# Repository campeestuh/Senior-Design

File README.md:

Circuit Wiring:

Rotary Encoder   --> FREENOVE ESP32 WROOM
> CLK (Output A) --> Pin 4 
> DT  (Output B) --> Pin 5 
> SW  (Switch)   --> Pin 16 
>  +  (VCC)      --> 5V 
> GND            --> GND

LCD 
VCC                 --> 5V
SDA (Serial Data)   --> Pin 21
SCL (Serial Clock)  --> Pin 22
GND                 --> GND

Button 
GND    --> GND
Signal --> Pin 19

Harness
STEP/PUL    --> Pin 15
DIRECTION   --> Pin 16
ENABLE      --> 5V

AUGER 
STEP/PUL    --> Pin 13
DIRECTION   --> Pin 14
ENABLE      --> 5V

AUGER 2 
STEP/PUL    --> Pin 33
DIRECTION   --> Pin 32
ENABLE      --> 5V

TREADMILL
STEP/PUL    --> Pin 27
DIRECTION   --> Pin 25
ENABLE      --> 5V

Arduino IDE
Board: ESP32 Wrover Module
How to get ESP32 Board Support:
- Go to File > Preferences
- In "Additional Board Manager URLs" add this URL:
https://dl.espressif.com/dl/package_esp32_index.json
- Click OK and save
- 
Install LiquidCrystal Library by Adafruit

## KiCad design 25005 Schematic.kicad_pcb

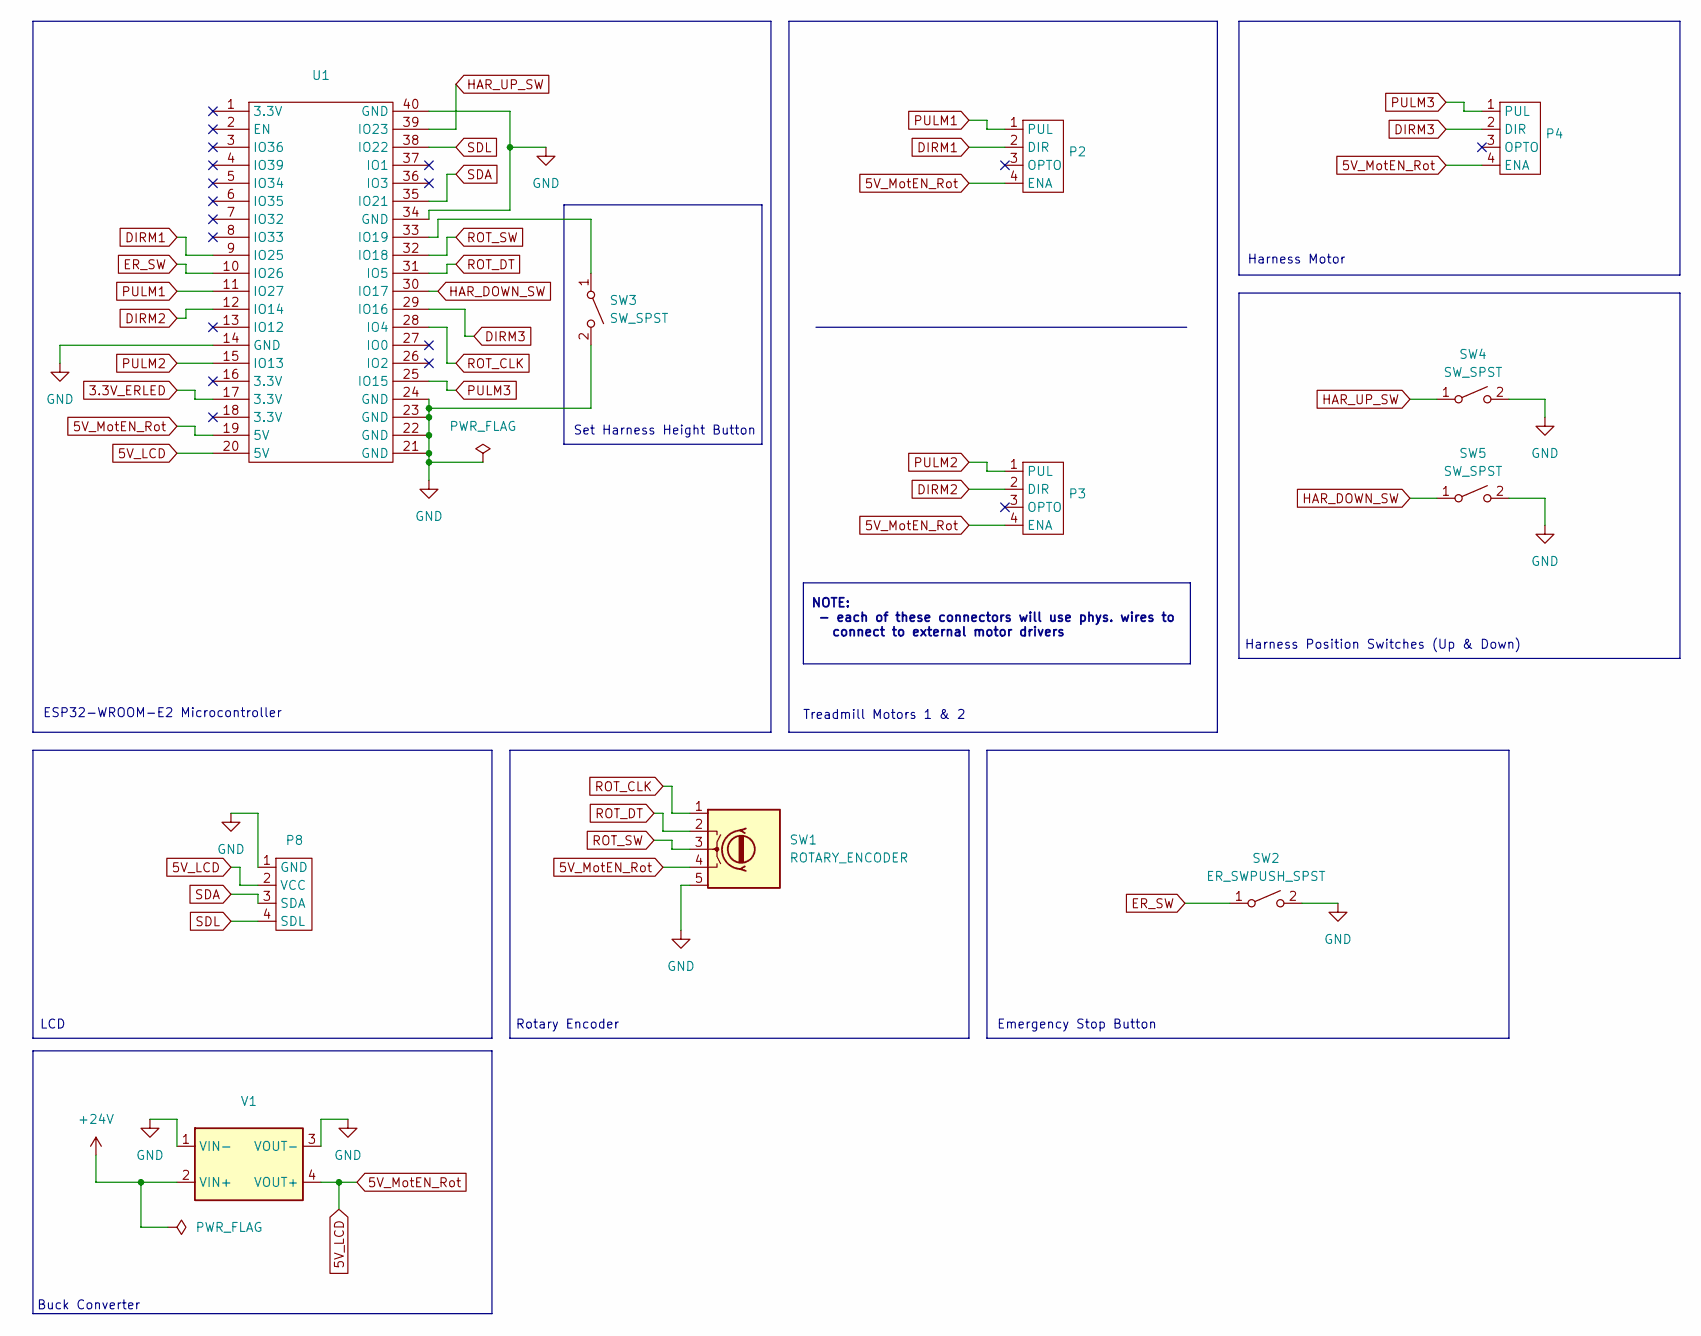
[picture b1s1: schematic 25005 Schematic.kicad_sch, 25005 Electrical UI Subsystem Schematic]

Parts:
P2, P3, P4: 3PIN_F_CONN_MOTORS
P8: 4PIN_F_CONN_LCD
SW1: ROTARY_ENCODER; 5PIN_F_CONN
SW2: ER_SWPUSH_SPST; ER_BUTTON
SW3, SW4, SW5: SW_SPST; SPST_SW
U1: ESP32_WROOM_32E
V1: BUCK_CONV

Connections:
3.3V_ERLED: U1.17 (3.3V)
5V_LCD: P2.4 (ENA), P3.4 (ENA), P4.4 (ENA), P8.2 (VCC), SW1.4 (5V), U1.19 (5V), U1.20 (5V), V1.4 (VOUT+)
+24V: V1.2 (VIN+)
DIRM1: P2.2 (DIR), U1.9 (IO25)
DIRM2: P3.2 (DIR), U1.12 (IO14)
DIRM3: P4.2 (DIR), U1.29 (IO16)
ER_SW: SW2.1, U1.10 (IO26)
GND: P8.1 (GND), SW1.5 (GND), SW2.2, SW3.2, SW4.2, SW5.2, U1.14 (GND), U1.21 (GND), U1.22 (GND), U1.23 (GND), U1.24 (GND), U1.34 (GND), U1.40 (GND), V1.1 (VIN-), V1.3 (VOUT-)
HAR_DOWN_SW: SW5.1, U1.30 (IO17)
HAR_UP_SW: SW4.1, U1.39 (IO23)
unnamed: SW3.1, U1.33 (IO19)
PULM1: P2.1 (PUL), U1.11 (IO27)
PULM2: P3.1 (PUL), U1.15 (IO13)
PULM3: P4.1 (PUL), U1.25 (IO15)
ROT_CLK: SW1.1 (CLK), U1.28 (IO4)
ROT_DT: SW1.2 (DT), U1.31 (IO5)
ROT_SW: SW1.3 (SW), U1.32 (IO18)
SDA: P8.3 (SDA), U1.35 (IO21)
SDL: P8.4 (SDL), U1.38 (IO22)

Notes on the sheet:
Harness Motor
ESP32-WROOM-E2 Microcontroller
Rotary Encoder
NOTE: - each of these connectors will use phys. wires to connect to external motor drivers
Set Harness Height Button
Harness Position Switches (Up & Down)
Emergency Stop Button
Treadmill Motors 1 & 2
Buck Converter
LCD

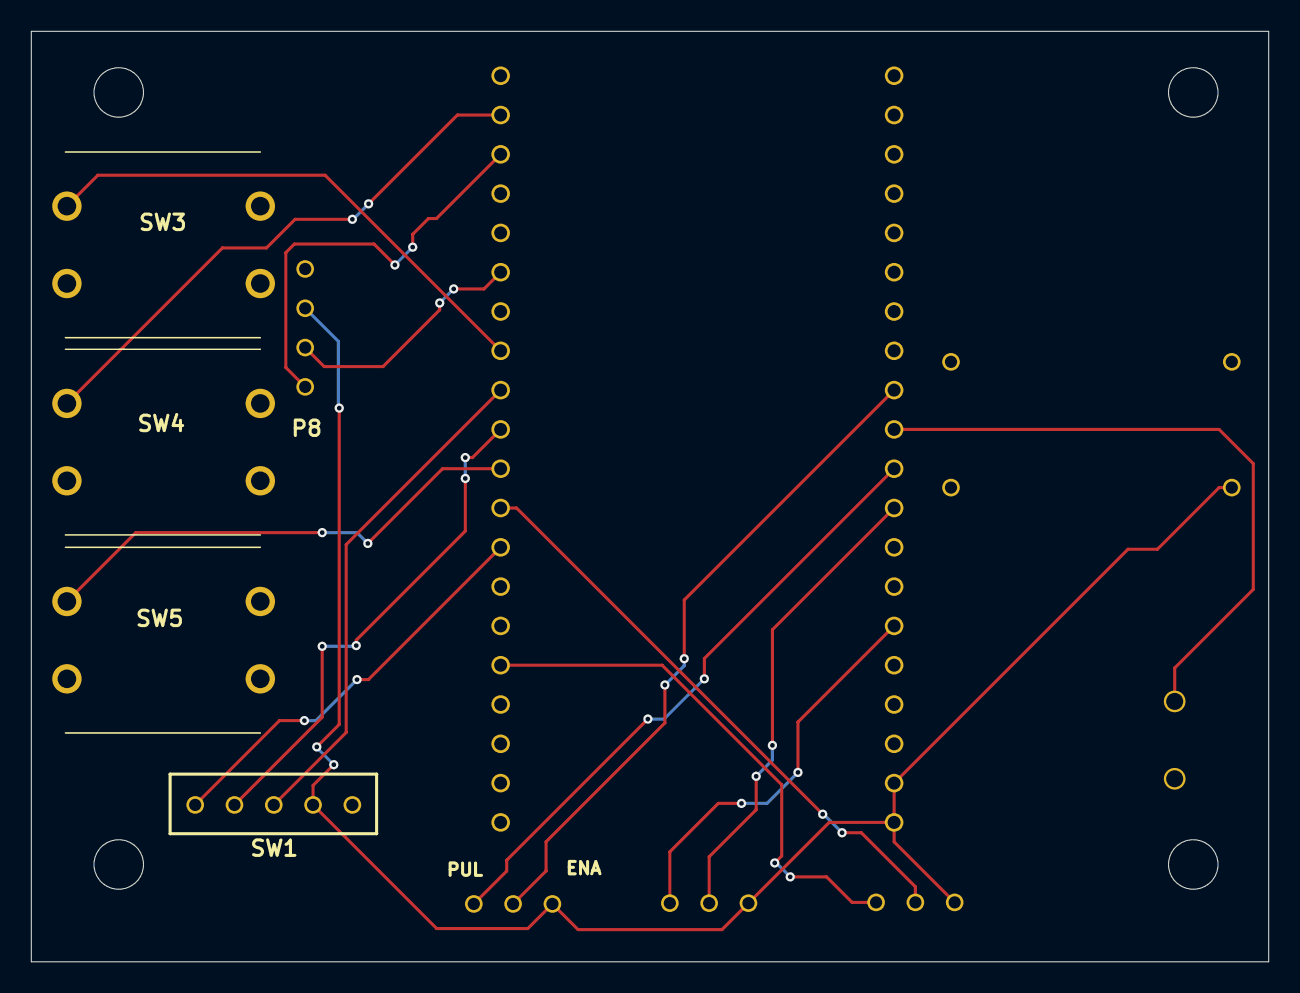
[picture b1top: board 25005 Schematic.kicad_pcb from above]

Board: 2 copper layers, 80.0 x 60.1 mm, 11 parts (1 on the bottom side), 17 nets.

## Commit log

2025-01-10 Update Senior_Design.ino
    New updated code. Still need to test Harness so i might need to fix it
2025-01-31 Create TestwFullAssembly,ino
2025-02-13 Update Senior_Design.ino
    Best iteration
2025-03-18 PCB & Schematic
2025-03-20 Create SeniorDesign2
    Added 2nd Auger Motor
2025-03-20 Rename SeniorDesign2 to Senior_Design2
2025-03-20 25005 Operating Manual
